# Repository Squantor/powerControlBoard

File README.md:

# Power Control Board
This repository contains the design files for a general purpose power control board usable for various applications:
* Controlling ovens/hotplates
* Lighting systems
* Soldering irons
In short, anything that requires power switching and possible line voltages.
## Structure
* [electronics](electronics/README.md) contains the power control boards and prototyping tryouts.
* [software](software/README.md) contains all the software used.
* [mechanical](mechanical/README.md) contains all the CAD drawings, mostly 3d printable objects.
* [documentation](documentation/README.md) contains all project documentation, logs, research, papers, datasheets and more.
## Cloning
This repository makes extensive use of submodules, use ```git clone --recurse-submodules https://github.com/Squantor/generic_project_template.git``` to clone everything in one go.

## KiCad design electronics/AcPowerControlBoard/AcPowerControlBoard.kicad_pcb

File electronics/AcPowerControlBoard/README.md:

# AC power control board
Power control board for isolated AC voltages, fits a small nuclone board
# HSI (Hardware Software Interface)
This applies to a project that has a embedded software component. Describe what each pin/bus does, what it is connected to, what its function is and some "safe" behaviour when starting up.
## TODO's
Still some things need to be done:
* Fill in this project description
* schematic entry 
* PCB layout
* Review with one night in between
* Produce at [OSHPARK](https://oshpark.com/)
* Assemble
* Test & characterise
* update Readme.md with pictures and BOM
## BOM
This is a list of hardware components. If just mentioned a generic component like a 1K 0402 resistor, just name it as such, free to substitute. If you need some special integrated IC's show some sources like Mouser, Digikey, Farnell, or LCSC

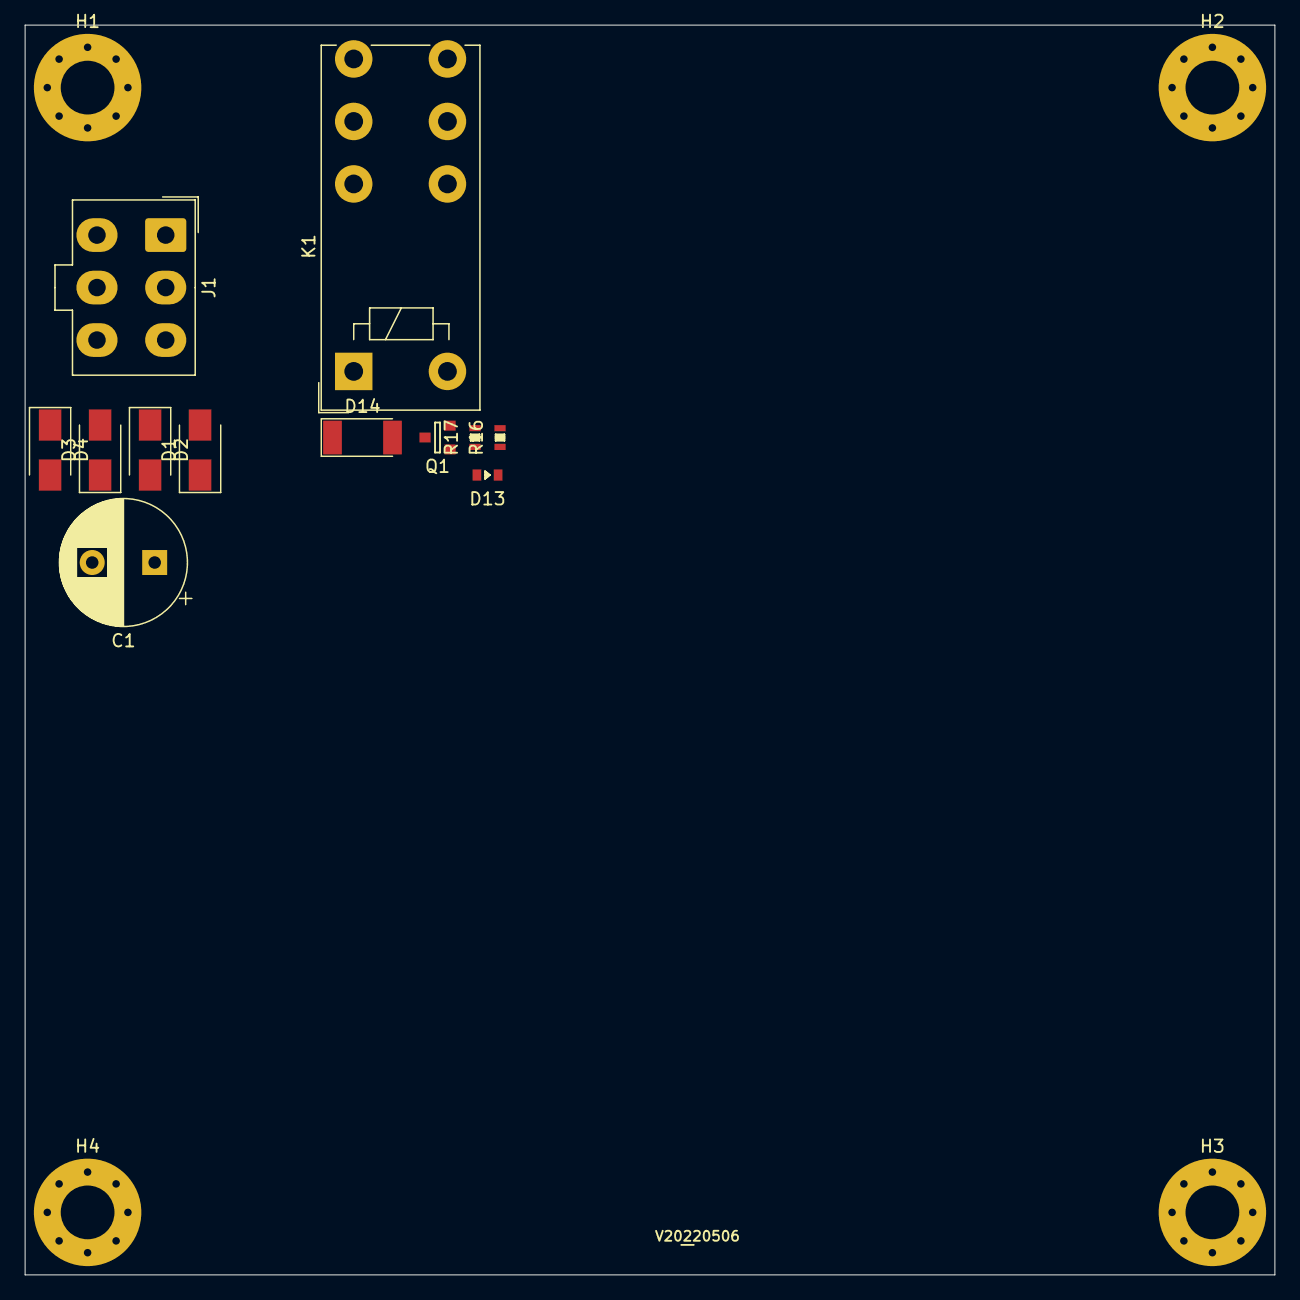
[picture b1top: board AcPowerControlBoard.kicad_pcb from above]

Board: 2 copper layers, 100.0 x 100.0 mm, 17 parts (0 on the bottom side), 11 nets, no tracks yet.

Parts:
C1: 470u; CP_Radial_D10.0mm_P5.00mm
D1, D2, D3, D4: 1N4001; D_SMA
D13: LED; LED_0603_hand
D14: LL4148; D_MELF
H1, H2, H3, H4: M4; MountingHole_4.3mm_M4_Pad_Via
J1: molex microfit; Molex_Mini-Fit_Jr_5566-06A_2x03_P4.20mm_Vertical
K1: FINDER-40.52; Relay_DPDT_Finder_40.52
N1: V20220506; Label_Generic
Q1: Q_NMOS_GSD; SOT23-3
R16: 1K; R_0603
R17: 10K; R_0603

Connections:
/AC_LP_1: D1.2 (A), D2.1 (K), J1.3
/AC_LP_2: D3.2 (A), D4.1 (K), J1.6
/AC_POWER_1: J1.1, J1.2, K1.21
/AC_POWER_2: J1.4, J1.5, K1.11
/safety relay/+12V: D14.1 (K), K1.A1
/safety relay/Coil: D14.2 (A), K1.A2, Q1.3 (D)
/safety relay/Enable: D13.2 (A), Q1.1 (G), R17.1
/safety relay/VSS: Q1.2 (S), R16.2, R17.2
unnamed: D13.1 (K), R16.1
VDD: C1.1, D1.1 (K), D3.1 (K)
VSS: C1.2, D2.2 (A), D4.2 (A)

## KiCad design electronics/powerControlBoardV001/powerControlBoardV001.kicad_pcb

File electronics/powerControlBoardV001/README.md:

# Power Control Board V001
First fully integrated power control board version. A choice was made to make the microcontroller external, for now.
# HSI (Hardware Software Interface)
TODO
## TODO's
Still some things need to be done:
* schematic entry 
* PCB layout
* Review with one night in between
* Produce at [OSHPARK](https://oshpark.com/)
* Assemble
* Test & characterise
* update Readme.md with pictures and BOM
## BOM
Most of my parts are sourced from LCSC, it seems the lowest effort way to get components at an affordable price.
* Hilink 12V module
* Triac
* 12V stepdown converter IC's
* Optocoupler
* 
## Pictures
TODO

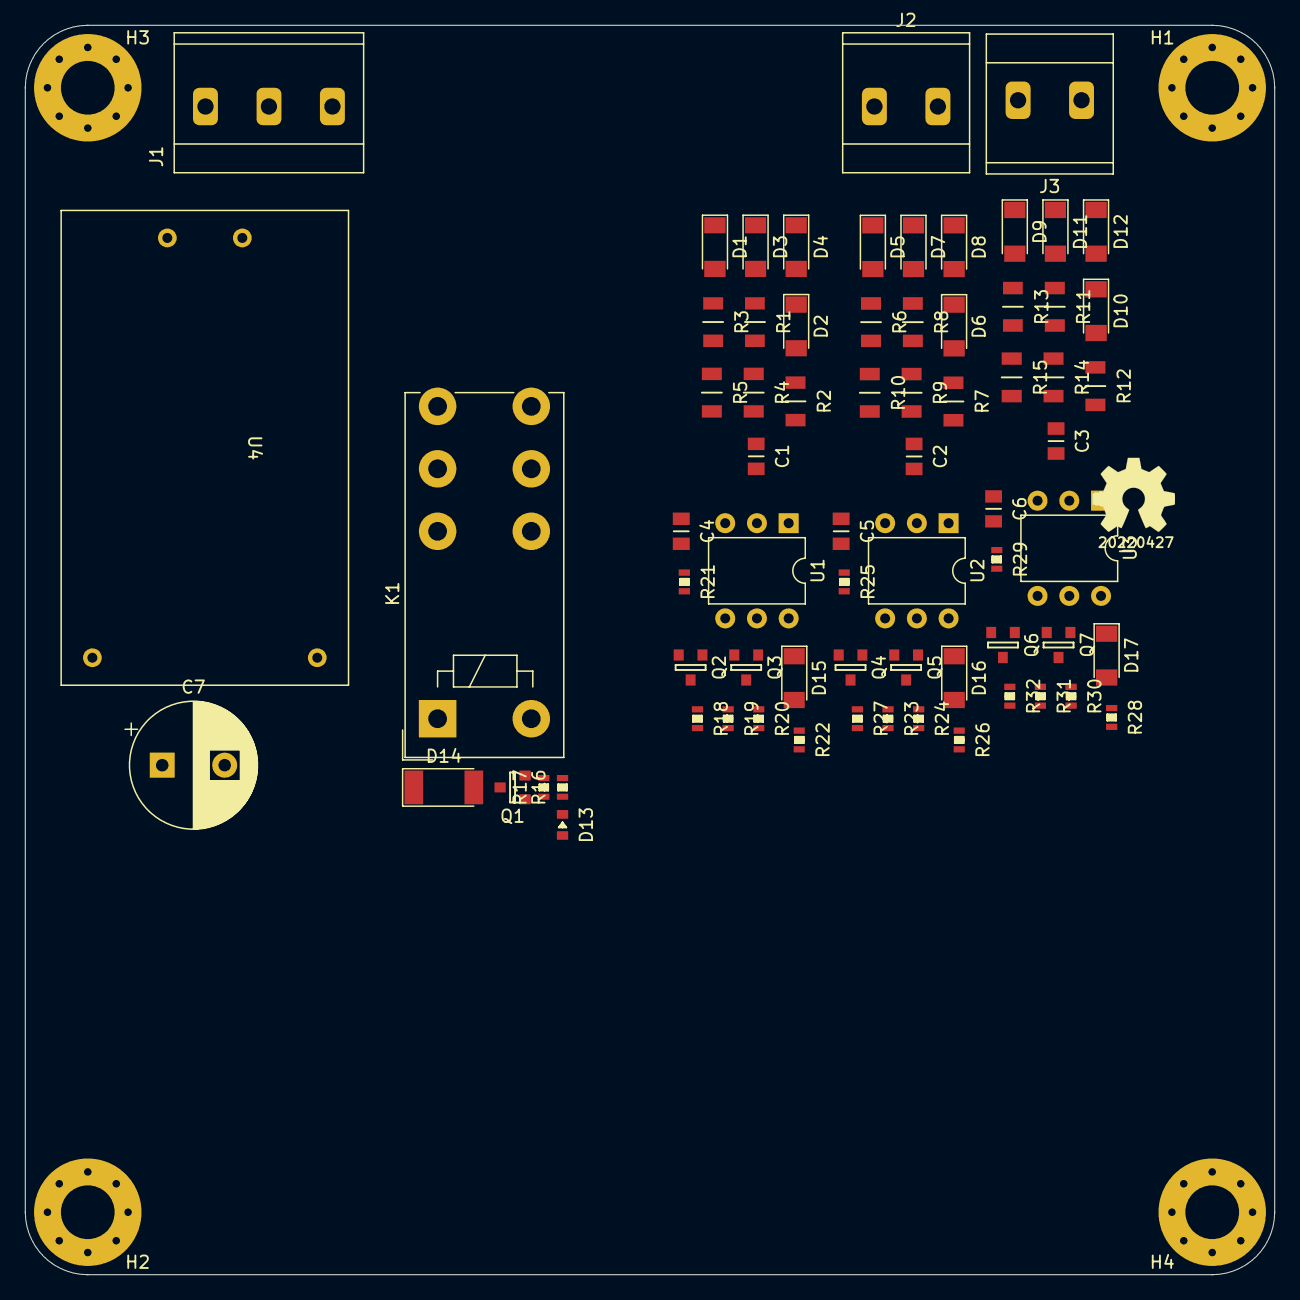
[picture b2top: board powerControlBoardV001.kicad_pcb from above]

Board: 2 copper layers, 100.0 x 100.0 mm, 77 parts (0 on the bottom side), 53 nets, no tracks yet.

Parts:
C1, C2, C3: 10n; C_0805
C4, C5, C6: 10u; C_0805
C7: 220u; CP_Radial_D10.0mm_P5.00mm
D1, D2, D3, D4, D5, D6, D7, D8, D9, D10, D11, D12, D15, D16, D17: 1N4148; D_MiniMELF
D13: LED; LED_0603_hand
D14: LL4148; D_MELF
H1, H2, H3, H4: M4; MountingHole_4.3mm_M4_Pad_Via
J1: Conn_01x03; MKDS_3conn_508pitch_1711725
J2, J3: Conn_01x02; MKDS_2conn_508pitch_1711725
K1: FINDER-40.52; Relay_DPDT_Finder_40.52
N1: 20220427; Label_Generic
N2: OHWLOGO; OSHW-Symbol_6.7x6mm_SilkScreen
Q1: Q_NMOS_GSD; SOT23-3
Q2, Q3, Q4, Q5, Q6, Q7: MMBT3904; SOT23-3
R1, R2, R3, R4, R6, R7, R8, R9, R11, R12, R13, R14: 100K; C_1206
R5, R10, R15: 22K; C_1206
R16, R18, R20, R22, R23, R25, R27, R28, R30, R32: 1K; R_0603
R17: 10K; R_0603
R19, R24, R29: 2.2M; R_0603
R21, R26, R31: 47; R_0603
U1, U2, U3: 4N28; DIP-6_W7.62mm
U4: HLK-5M12; 5MXX_series

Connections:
+3V3: R21.1, R22.1, R26.1, R27.1, R31.1, R32.1
/L_in: J1.1, K1.21, R1.2, U4.1 (Line)
/L_out1: J2.1, R6.2
/L_out2: J3.1, R11.2
/N_in: J1.3, K1.11, R2.2, U4.2 (Neutral)
/N_out1: J2.2, R7.2
/N_out2: J3.2, R12.2
/Sheet62699DAD/+12V: D14.1 (K), K1.A1
/Sheet62699DAD/Coil: D14.2 (A), K1.A2, Q1.3 (D)
/Sheet62699DAD/Enable: D13.2 (A), Q1.1 (G), R17.1
/Sheet62699DAD/VSS: Q1.2 (S), R16.2, R17.2
/VDD: C7.1, U4.4 (VDD)
/VSS: C7.2, Q3.2 (E), Q5.2 (E), Q7.2 (E), R20.2, R25.2, R30.2, U4.3 (VSS)
/ZC_in: Q3.3 (C), R22.2
/ZC_out1: Q5.3 (C), Q7.3 (C), R27.2, R32.2
Earth: H1.1, H2.1, H3.1, H4.1, J1.2
unnamed: C1.1, D2.2 (A), D4.1 (K), R3.1
unnamed: C1.2, D1.2 (A), D3.1 (K), R4.1
unnamed: C2.1, D6.2 (A), D8.1 (K), R8.1
unnamed: C2.2, D5.2 (A), D7.1 (K), R9.1
unnamed: C3.1, D10.2 (A), D12.1 (K), R13.1
unnamed: C3.2, D9.2 (A), D11.1 (K), R14.1
unnamed: C4.1, D1.1 (K), D2.1 (K), R5.2, R18.2
unnamed: C4.2, D15.2 (A), Q2.2 (E)
unnamed: C5.1, D5.1 (K), D6.1 (K), R10.2, R23.2
unnamed: C5.2, D16.2 (A), Q4.2 (E)
unnamed: C6.1, D9.1 (K), D10.1 (K), R15.2, R28.2
unnamed: C6.2, D17.2 (A), Q6.2 (E)
unnamed: D11.2 (A), D12.2 (A), D17.1 (K), Q6.1 (B), R15.1
unnamed: D13.1 (K), R16.1
unnamed: D3.2 (A), D4.2 (A), D15.1 (K), Q2.1 (B), R5.1
unnamed: D7.2 (A), D8.2 (A), D16.1 (K), Q4.1 (B), R10.1
unnamed: Q2.3 (C), U1.2
unnamed: Q3.1 (B), R19.2, R20.1, U1.4
unnamed: Q4.3 (C), U2.2
unnamed: Q5.1 (B), R24.2, R25.1, U2.4
unnamed: Q6.3 (C), U3.2
unnamed: Q7.1 (B), R29.2, R30.1, U3.4
unnamed: R1.1, R3.2
unnamed: R2.1, R4.2
unnamed: R6.1, R8.2
unnamed: R7.1, R9.2
unnamed: R11.1, R13.2
unnamed: R12.1, R14.2
unnamed: R18.1, U1.1
unnamed: R19.1, U1.6
unnamed: R21.2, U1.5
unnamed: R23.1, U2.1
unnamed: R24.1, U2.6
unnamed: R26.2, U2.5
unnamed: R28.1, U3.1
unnamed: R29.1, U3.6
unnamed: R31.2, U3.5

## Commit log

2021-04-16 initial population of power control board electronics, software, mechanical, documentation
2021-04-16 updated gitignore and added documentation folder
2021-04-25 updated build system
2021-04-25 fixed doxygen output
2021-04-25 correctly find symbols
2021-04-25 added default task label
2021-04-25 removed old gpio blinking code
2021-04-30 updated PCB library
2021-04-30 initial creation of board V0 and V1
2021-04-30 updated readmes
2021-04-30 added phoenix contact terminal blocks with courtyards
2021-04-30 created initial schematic and connections and first PCB outline
2021-05-01 added net filtering subschematic
2021-05-01 added net filtering components and fuse
2021-05-01 added net filtering parts to PCB, placed, routed, silk optimized
2022-04-27 initial cleanup
2022-04-27 updated versionnumber and cleanup of parts, WIP overall architecture
2022-04-27 started with safety relay pins
2022-04-27 added more submodules
2022-04-27 added solid state relay submodule
2022-04-27 WIP: connections
2022-04-27 completed top level power section connections
2022-04-27 updated LV sections
2022-04-27 imported initial components into PCB
2022-05-03 dont need to save caches
2022-05-03 ignoring fp caches
2022-05-03 created safety relay circuit
2022-05-03 added stuff to board, fixed missing footprint
2022-05-03 added full zerocross detector
2022-05-05 updated urls to use ssh instead of https
2022-05-05 added hilink lib and started with kicad6 conversion
2022-05-05 added kicad 6 temporaries
2022-05-05 Added more ignorable files
2022-05-05 conversion to kicad 6
2022-05-05 updated pcb to kicad 6 format
2022-05-05 newer pcb library
2022-05-05 added hv psu section
2022-05-05 switched to new symbol libraries
2022-05-06 project reorganisation
2022-05-06 started with AC control board
2022-05-06 added safety relay and rectifier subsystem
